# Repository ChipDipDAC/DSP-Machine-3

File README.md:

# DSP-Machine-3<br>
<a class="link" href="https://www.chipdip.ru/catalog-show/for-you-projects?p.0=ChipDipDac"><strong>DSP Machine 3</strong></a> - стример, цифроаналоговый преобразователь ЦАП, аудиопроцессор, для микрокомпьютера Raspberry Pi.<br />
Для построения стримера вы можете использовать любой микрокомпьютер Raspberry Pi. Микрокомпьютер устанавливается на 40-пиновый разъем аудио карты. В качестве ПО используйте любой плеер или ОС образ, которых записан на микроSD карточку для Raspberry Pi. Операционные системы автоматически определяют аудиокарту ChipDip DAC и настраивают вывод звука именно на неё. В некоторых плеерах может понадобится выбрать в качестве устройства вывода звука - ChipDip DAC.<br />
<br />
- Plug and Play не требует пайки<br />
- Совместим с Raspberry Pi 4<br />
- Официальная поддержка RaspberryPi OS / Volumio3 / rAudio1 / Album Player / OpenELEC / Manjaro OS / MoOde и другими.<br />
- Высококачественный аудиопроцессор ADAU1452 и ЦАП AD1934.<br />
- Разъемы аудиовыхода: 2 x XLR (левый и правый), SPDIF, Coaxial<br />
- Встроенная EEPROM для автоматической настройки ОС (с защитой от записи).<br />
- Автоматическое переключение частот в соответствии с входными сигналами I2S.<br />
- Диапазон частот дискретизации и разрядности от 44,1кГц/16 бит до 192кГц/32 бит<br />
- Цветова индикация частот дискретизации<br />
- Совместим с ПО SigmaStudio и ChipStudio для перестройки аудиопроцессора<br />
Задать вопросы можно на форуме в разделе <a class="link" href="https://forum.chipdip.ru/index.php#chipdip-dac.39">ChipDip DAC</a>
<p></p>

<p></p>

<h2>Что под крышкой *</h2>

<p></p>

<p></p>
* Микрокомпьютер Raspberry Pi в комплект не входит.

<h2>Цветовая индикация частоты преобразования (sample rate)</h2>

<table class="user_t">
	<tbody>
		<tr>
			<td class="tcenter">
			<p><strong>Sample Rate</strong></p>
			</td>
			<td class="tcenter">
			<p><strong>Цвет индикатора</strong></p>
			</td>
		</tr>
		<tr>
			<td class="tcenter">44.1 кГц</td>
			<td class="tcenter"></td>
		</tr>
		<tr>
			<td class="tcenter">48 кГц</td>
			<td class="tcenter"></td>
		</tr>
		<tr>
			<td class="tcenter">88.2 кГц</td>
			<td class="tcenter"></td>
		</tr>
		<tr>
			<td class="tcenter">96 кГц</td>
			<td class="tcenter"></td>
		</tr>
		<tr>
			<td class="tcenter">176.4 кГц</td>
			<td class="tcenter"></td>
		</tr>
		<tr>
			<td class="tcenter">192 кГц</td>
			<td class="tcenter"></td>
		</tr>
	</tbody>
</table>

<h2>Сравнительная таблица</h2>

<table class="user_t">
	<tbody>
		<tr>
			<td class="tcenter">&nbsp;</td>
			<td class="tcenter">DSP Machine 1</td>
			<td class="tcenter">DSP Machine 2</td>
			<td class="tcenter">DSP Machine 3</td>
		</tr>
		<tr>
			<td class="tcenter">Темброблок</td>
			<td class="tcenter">+</td>
			<td class="tcenter">+</td>
			<td class="tcenter">+</td>
		</tr>
		<tr>
			<td class="tcenter">SuperBass</td>
			<td class="tcenter">+</td>
			<td class="tcenter">+</td>
			<td class="tcenter">+</td>
		</tr>
		<tr>
			<td class="tcenter">Mute</td>
			<td class="tcenter">+</td>
			<td class="tcenter">+</td>
			<td class="tcenter">+</td>
		</tr>
		<tr>
			<td class="tcenter">Блок питания</td>
			<td class="tcenter">+</td>
			<td class="tcenter">+</td>
			<td class="tcenter">+</td>
		</tr>
		<tr>
			<td class="tcenter">Корректное выключение</td>
			<td class="tcenter">+</td>
			<td class="tcenter">+</td>
			<td class="tcenter">+</td>
		</tr>
		<tr>
			<td class="tcenter">Линейный выход</td>
			<td class="tcenter">-</td>
			<td class="tcenter">+</td>
			<td class="tcenter">+</td>
		</tr>
		<tr>
			<td class="tcenter">Усилитель мощности</td>
			<td class="tcenter">+</td>
			<td class="tcenter">-</td>
			<td class="tcenter">-</td>
		</tr>
		<tr>
			<td class="tcenter">Выход SPDIF</td>
			<td class="tcenter">-</td>
			<td class="tcenter">-</td>
			<td class="tcenter">+</td>
		</tr>
		<tr>
			<td class="tcenter">Выход Toslink</td>
			<td class="tcenter">-</td>
			<td class="tcenter">-</td>
			<td class="tcenter">+</td>
		</tr>
		<tr>
			<td class="tcenter">SigmaStudio</td>
			<td class="tcenter">+</td>
			<td class="tcenter">-</td>
			<td class="tcenter">+</td>
		</tr>
		<tr>
			<td class="tcenter">PurePathStudio</td>
			<td class="tcenter">-</td>
			<td class="tcenter">+</td>
			<td class="tcenter">-</td>
		</tr>
		<tr>
			<td class="tcenter">ChipStudio</td>
			<td class="tcenter">+</td>
			<td class="tcenter">+</td>
			<td class="tcenter">+</td>
		</tr>
	</tbody>
</table>
<br />

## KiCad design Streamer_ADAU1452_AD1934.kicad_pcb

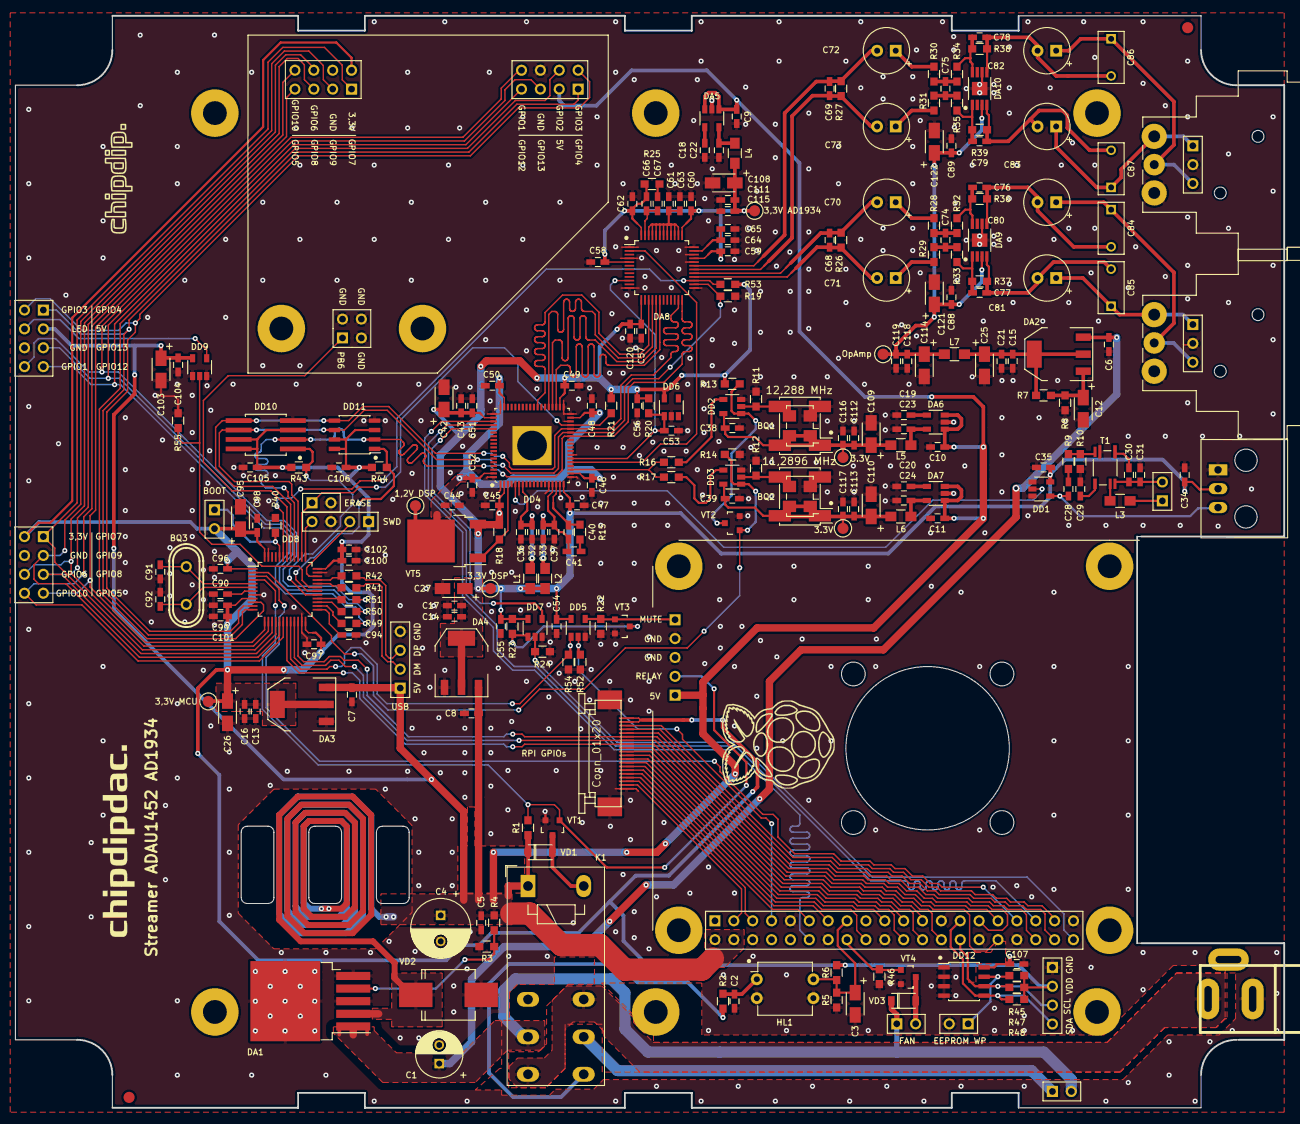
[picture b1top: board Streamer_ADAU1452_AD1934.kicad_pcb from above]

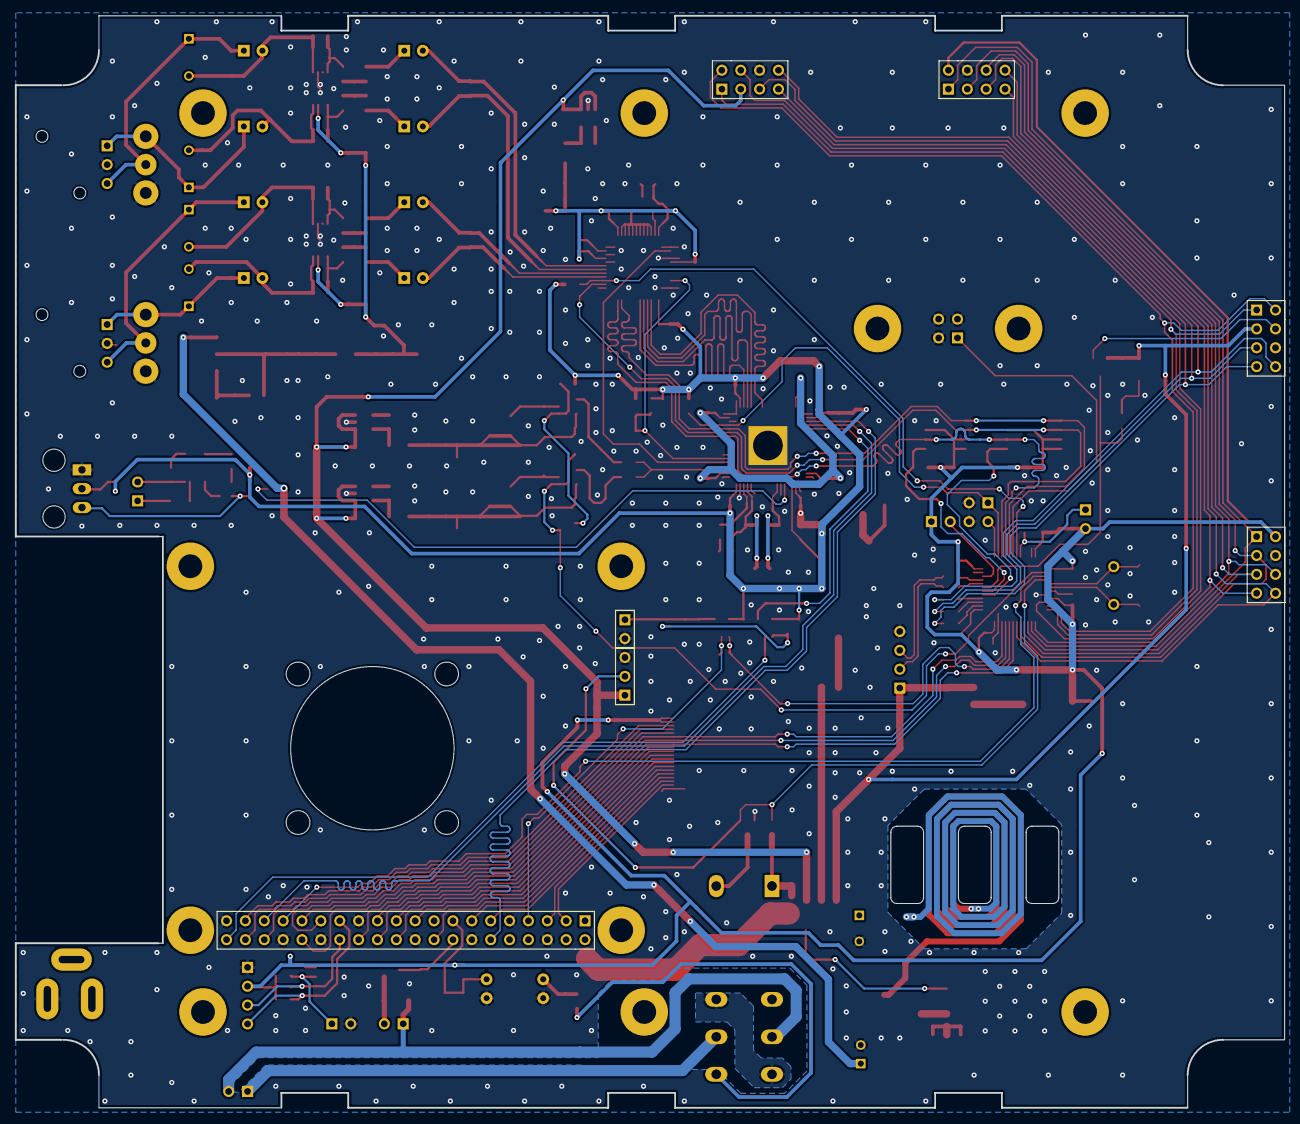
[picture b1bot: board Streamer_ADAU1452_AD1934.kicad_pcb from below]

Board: 2 copper layers, 170.8 x 147.0 mm, 252 parts (7 on the bottom side), 148 nets.

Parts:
BQ1: 12,288MHz; Oscillator_SMD_Fordahl_DFAS2-4Pin_7.3x5.1mm_HandSoldering
BQ2: 11,2896MHz; Oscillator_SMD_Fordahl_DFAS2-4Pin_7.3x5.1mm_HandSoldering
BQ3: 8 Mhz; CRYST_hc-49u_mm
BQ4: 12,288MHz; Oscillator_SMD_EuroQuartz_XO53-4Pin_5.0x3.2mm_HandSoldering
BQ5: 11,2896MHz; Oscillator_SMD_EuroQuartz_XO53-4Pin_5.0x3.2mm_HandSoldering
C1: 100u; C_Radial_D6.3_L11.2_P2.5
C2, C32, C33, C43, C44, C63, C65, C120: 10u; C_0603_HandSoldering
C3, C12, C25, C26, C27, C42, C95, C103, C108, C109, C110, C114, C121, C122: 4.7u; TantalC_SizeA_EIA-3216_mm
C4: 1000u; C_Radial_D8_L11.5_P3.5
C5, C6, C7, C8, C9, C10, C11, C13, C14, C15, C16, C17, C21, C22, C23, C24, C96, C101, C102, C111, C112, C113, C118: 2.2u; C_0603_HandSoldering
C18, C19, C20, C28: 0.01u; C_0603_HandSoldering
C29, C30, C34, C35, C36, C37, C38, C39, C45, C46, C47, C48, C49, C50, C51, C52, C53, C54, C55, C56, C57, C58, C59, C60, C61, C62, C64, C88, C89, C90, C97, C98, C99, C100, C104, C105, C106, C107, C115, C116, C117, C119: 0.1u; C_0603_HandSoldering
C31, C91, C92: 22p; C_0603_HandSoldering
C40, C76, C77, C78, C79: 150p; C_0603_HandSoldering
C41, C67: 5n6; C_0603_HandSoldering
C66: 390p; C_0603_HandSoldering
C68, C69: 1n; C_0603_HandSoldering
C70, C71, C72, C73, C80, C81, C82, C83: 10u; CP_Radial_Tantal_D6.0mm_P2.50mm
C74, C75: 470p; C_0603_HandSoldering
C84, C85, C86, C87: 0.47u; C_Rect_L7_W3.5_P5
C94: 47p; C_0603_HandSoldering
DA1: LM2596S-ADJ; TO-263-5_TabPin3
DA2, DA3, DA4: LM1117-3.3; SOT-223
DA5, DA6, DA7: LP2985-3.3; SOT-23-5_mm
DA8: AD1934; LQFP-48_7x7mm_Pitch0.5mm
DA9, DA10: OPA1632; VSSOP-8
DD1, DD2, DD3, DD7: 74LVC1G125; SOT-23-5_mm
DD4: ADAU1452; LFCSP72_10x10_EP_Handsoldering
DD5: NC7S08M5X; SOT-23-5_mm
DD6: ADM6316; SOT-23-5_mm
DD8: STM32L433CCTx; LQFP-48_7x7mm_Pitch0.5mm
DD9: MC74VHC1GT125; SOT-23-5_mm
DD10: 25LCxxx; SOIC-8_combo_Pitch1.27mm
DD11: 25LCxxx; SOIC-8_3.9x4.9mm_Pitch1.27mm
DD12: 24LC64; SOIC-8_3.9x4.9mm_Pitch1.27mm
HL1: P814; DIP-4_W7.62mm
K1: RTE2xxxx; Relay_DPDT_Schrack-RT2-FormC_RM5mm
L1, L2, L3, L4, L5, L6, L7: L; R_0805_HandSoldering
P3, P4, P5, P6, P7, P8, P9: Conn_01x01; Measurement_Point_Round-SMD-Pad_Small
R1, R6, R7, R8, R11, R12, R13, R14, R19, R20, R21, R22, R23, R24, R36, R37, R38, R39, R40, R43, R44, R45, R46, R49, R50, R51, R52, R53, R54, R55: 10k; R_0603
R2: 2k; R_0603
R3, R18: 1k; R_0603
R4: 3k; R_0603
R5: 15k; R_0603
R9: 470R; R_0603
R10: 110R; R_0603
R15: 4k32; R_0603
R16, R17: 51R; R_0603
R25: 560; R_0603
R26, R27: 100k; R_0603
R28, R29, R30, R31, R32, R33, R34, R35: 2k2; R_0603
R41, R42: 22; R_0603
R47, R48: 4k7; R_0603
T1: ALT4532M; ALT4532
VD1, VD3: D; SOD-123
VD2: D_Schottky; DIODE_SMC_Handsoldering
VT1, VT2, VT3, VT4: BSS138; SOT-23_mm
VT5: STD2805; TO-252-2
XP1, XP14, XP15: Conn_01x03; Pin_Header_Straight_1x03_mm
XP2: Conn_01x03; Optic_FCR6842031T
XP3, XP6, XP8, XP9, XP11, XP13: Conn_01x02; Pin_Header_Straight_1x02_mm
XP4, XP5: XLR3; Jack_XLR_Neutrik_NC3MAAH-1_Horizontal
XP7, XP10, XP12: Conn_01x04; Pin_Header_Straight_1x04_mm
XS1: Conn_01x03; JACK_DC
XS2: Conn_01x02; Pin_Header_Straight_1x02_mm
XS3: Conn_02x20_Odd_Even; Pin_Header_Straight_2x20_mm
XS4, XS5, XS7, XS8: Conn_02x04_Odd_Even; Pin_Header_Straight_2x04_mm
XS6: Conn_01x20; CONN20
XS9: Conn_02x02_Odd_Even; Pin_Header_Straight_2x02_mm

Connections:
5V: C4.1, C5.1, C7.1, C8.1, C9.1, C10.1, C11.1, C103.1, C104.1, DA1.2, DA3.3, DA4.3, DA5.1, DA5.3, DA6.1, DA6.3, DA7.1, DA7.3, DD9.5, K1.A1, R1.1, R4.1, VD1.1, VD2.1, XP1.1, XP10.1, XS3.2, XS3.4, XS5.3, XS8.3
12V: K1.14, K1.22, XS1.1
BCLK: DD4.57, XS3.12
BOOT: DD8.44, R40.1, XP6.1
DATA: DD7.2, R24.2, XS3.40
DSP_BCLK0: DA8.17, DD4.40
DSP_LR0: DA8.18, DD4.39
DSP_RST: C53.1, DA8.10, DD4.24, DD6.1, R20.2
DSP_SDATA0: DA8.16, DD4.41
DSP_SDATA1: DA8.15, DD4.44
DVDD: C44.1, C46.1, C48.1, C50.1, C52.1, DD4.20, DD4.35, DD4.53, DD4.71, P6.1, VT5.2
FAN: R46.1, VT4.1, XS3.16
GEN_SEL: DD3.1, DD8.2, R14.1, VT2.1
GND: BQ1.2, BQ2.2, BQ4.2, BQ5.2, C1.2, C2.2, C3.2, C4.2, C5.2, C6.2, C7.2, C8.2, C9.2, C10.2, C11.2, C12.2, C13.2, C14.2, C15.2, C16.2, C17.2, C18.2, C19.2, C20.2, C21.2, C22.2, C23.2, C24.2, C25.2, C26.2, C27.2, C29.2, C31.2, C32.2, C33.2, C34.2, C35.2, C36.2, C37.2, C38.2, C39.2, C42.2, C43.2, C44.2, C45.2, C46.2, C47.2, C48.2, C49.2, C50.2, C51.2, C52.2, C53.2, C54.2, C55.2, C56.2, C57.2, C58.2, C59.2, C60.2, C61.2, C62.2, C63.2, C64.2, C65.2, C88.1, C89.1, C90.2, C91.2, C92.2, C94.2, C95.2, C96.2, C97.2, C98.2, C99.2, C100.2, C101.2, C102.2, C103.2, C104.2, C105.2, C106.2, C107.2, C108.2, C109.2, C110.2, C111.2, C112.2, C113.2, C114.2, C115.2, C116.2, C117.2, C118.2, C119.2, C120.2, C121.2, C122.2, DA1.3, DA1.5, DA3.1, DA4.1, DA5.2, DA6.2, DA7.2, DA8.1, DA8.4, DA8.12, DA8.25, DA8.32, DA8.34, DA8.36, DA9.6, DA9.9, DA10.6, DA10.9, DD1.1, DD1.3, DD2.3, DD3.3, DD4.1, DD4.6, DD4.14, DD4.17, DD4.19, DD4.25, DD4.34, DD4.36, DD4.37, DD4.54, DD4.55, DD4.72, DD4.73, DD5.3, DD6.2, DD7.3, DD8.8, DD8.23, DD8.35, DD8.47, DD9.1, DD9.3, DD10.4, DD11.4, DD12.1, DD12.2, DD12.3, DD12.4, HL1.2, HL1.3, R3.1, R5.2, R8.2, R10.2, R11.1, R12.1, R14.2, R19.1, R22.2, R24.1, R40.2, R46.2, R52.1, R54.1, R55.2, T1.2, VD2.2, VT1.2, VT2.2, VT3.2, VT4.2, XP1.3, XP2.1, XP3.2, XP4.1, XP5.1, XP7.3, XP8.2, XP10.4, XP11.2, XP12.1, XP14.2, XP15.2, XS1.2, XS3.6, XS3.9, XS3.14, XS3.20, XS3.25, XS3.30, XS3.34, XS3.39, XS4.4, XS5.6, XS6.20, XS7.4, XS8.6, XS9.2, XS9.3, XS9.4
GPIO0: DA8.27, DD8.43, R53.2
GPIO1: R51.1, XS5.8, XS8.8
GPIO2: DD8.10, XS8.4
GPIO3: DD8.11, XS5.2, XS8.2
GPIO4: DD8.12, XS5.1, XS8.1
GPIO5: DD8.13, XS4.7, XS7.7
GPIO6: DD8.14, XS4.6, XS7.6
GPIO7: DD8.15, XS4.1, XS7.1
GPIO8: DD8.16, XS4.5, XS7.5
GPIO9: DD8.17, XS4.3, XS7.3
GPIO10: DD8.18, XS4.8, XS7.8
GPIO12: R49.1, XS5.7, XS8.7
GPIO13: R50.1, XS5.5, XS8.5
ID_SCL: DD12.6, R47.2, XP12.3, XS3.28
ID_SDA: DD12.5, R48.2, XP12.4, XS3.27
LED_OUT: DD9.4, XS5.4
LR: DD4.58, XS3.35
MCLK_OUT: DA8.2, DD4.23
MUTE: DD5.2, R52.2, XS3.7
MUTE2: DD5.1, DD8.20, R54.2
MUTE_OUT: DA9.7, DA10.7, DD5.4, R22.1, VT3.1, XP3.1
unnamed: BQ1.3, BQ4.3, DD2.2, R11.2
unnamed: BQ2.3, BQ5.3, DD3.2, R12.2
unnamed: BQ3.1, C91.1, DD8.5
unnamed: BQ3.2, C92.1, DD8.6
unnamed: C2.1, HL1.1, R2.2
unnamed: C12.1, DA2.1, R7.2, R8.1
unnamed: C15.1, C21.1, C25.1, DA2.2, DA2.4, L7.1, R7.1
unnamed: C18.1, DA5.4
unnamed: C19.1, DA6.4
unnamed: C20.1, DA7.4
unnamed: C22.1, DA5.5, L4.1
unnamed: C23.1, DA6.5, L5.1
unnamed: C24.1, DA7.5, L6.1
unnamed: C28.1, R9.2
unnamed: C29.1, T1.6
unnamed: C30.1, T1.3
unnamed: C30.2, C31.1, T1.4, XS2.2
unnamed: C32.1, C36.1, DD4.7, L1.2
unnamed: C33.1, C37.1, C40.1, C41.1, DD4.15, L2.2
unnamed: C40.2, DD4.16, R15.2
unnamed: C41.2, R15.1
unnamed: C61.1, C63.1, DA8.38, DA8.39, DA8.40, DA8.41, DA8.42, DA8.43, DA8.44, DA8.45, DA8.46
unnamed: C64.1, C65.1, DA8.35
unnamed: C66.1, C67.1, DA8.47
unnamed: C67.2, R25.1
unnamed: C68.1, C70.2, DA8.29, R26.1
unnamed: C68.2, C71.2, DA8.28, R26.2
unnamed: C69.1, C72.2, DA8.31, R27.1
unnamed: C69.2, C73.2, DA8.30, R27.2
unnamed: C70.1, R28.1
unnamed: C71.1, R29.1
unnamed: C72.1, R30.1
unnamed: C73.1, R31.1
unnamed: C74.1, R28.2, R32.1
unnamed: C74.2, R29.2, R33.1
unnamed: C75.1, R30.2, R34.1
unnamed: C75.2, R31.2, R35.1
unnamed: C76.1, C80.2, C84.2, DA9.5, R36.2
unnamed: C76.2, DA9.8, R32.2, R36.1
unnamed: C77.1, C81.2, C85.2, DA9.4, R37.2
unnamed: C77.2, DA9.1, R33.2, R37.1
unnamed: C78.1, C82.2, C86.2, DA10.5, R38.2
unnamed: C78.2, DA10.8, R34.2, R38.1
unnamed: C79.1, C83.2, C87.2, DA10.4, R39.2
unnamed: C79.2, DA10.1, R35.2, R39.1
unnamed: C80.1, C84.1, XP4.3, XP14.3
unnamed: C81.1, C85.1, XP4.2, XP14.1
unnamed: C82.1, C86.1, XP5.3, XP15.3
unnamed: C83.1, C87.1, XP5.2, XP15.1
unnamed: C94.1, DD8.25
unnamed: DA1.4, R3.2, R4.2
unnamed: DD1.2, DD4.5
unnamed: DD2.1, R13.2, VT2.3
unnamed: DD2.4, R16.2
unnamed: DD3.4, R17.2
unnamed: DD4.3, R18.2, VT5.1
unnamed: DD4.21, R16.1, R17.1
unnamed: DD7.1, R23.2, VT3.3
unnamed: DD8.26, R49.2
unnamed: DD8.27, R50.2
unnamed: DD8.28, R51.2
unnamed: DD8.31, DD9.2, R55.1
unnamed: DD8.32, R41.1
unnamed: DD8.33, R42.1
unnamed: DD12.7, R45.2, XP8.1
unnamed: K1.21, XP13.1
unnamed: K1.24, R2.1
unnamed: K1.A2, VD1.2, VT1.3
unnamed: L3.1, T1.5
unnamed: L3.2, XS2.1
unnamed: R9.1, R10.1, T1.1
unnamed: VD3.2, VT4.3, XP9.2
ON_OFF: C3.1, HL1.4, R5.1, R6.2, XS3.15
PB6: DD8.42, XS9.1
PWR_EVENT: DD8.3, XS3.33
RAS_GPIO2: XS3.3, XS6.19
RAS_GPIO3: XS3.5, XS6.18
RAS_GPIO7: XS3.26, XS6.9
RAS_GPIO8: XS3.24, XS6.11
RAS_GPIO9: XS3.21, XS6.12
RAS_GPIO10: XS3.19, XS6.14
RAS_GPIO11: XS3.23, XS6.10
RAS_GPIO16: XS3.36, XS6.5
RAS_GPIO17: XS3.11, XS6.17
RAS_GPIO20: XS3.38, XS6.4
RAS_GPIO25: XS3.22, XS6.13
RAS_GPIO26: XS3.37, XS6.3
RELAY: DD8.4, R1.2, VT1.1, XP1.2
RES0: XS3.18, XS6.15
RES1: XS3.13, XS6.16
RST: C90.1, DD8.7
SDATA_IN0: DD4.59, DD7.4
SPDIF_OUT: C28.2, DD1.4, XP2.3
SPI1_MISO: DA8.24, DD4.30, DD8.40, DD10.2, DD11.2
SPI1_MOSI: DA8.23, DD4.32, DD8.41, DD10.5, DD11.5
SPI1_NSS1: DD4.33, DD8.38, R21.2, XP11.1
SPI1_NSS2: DD8.29, DD10.1, R43.2
SPI1_NSS3: DD8.30, DD11.1, R44.2
SPI1_SCK: DA8.26, DD4.31, DD8.39, DD10.6, DD11.6, R19.2
SR0: DD8.22, XS3.29, XS6.6
SR1: DD8.21, XS3.31, XS6.7
SR2: DD8.19, XS3.32, XS6.8
SWCLK: DD8.37, XP7.4
SWDIO: DD8.34, XP7.2
USB_DM: R41.2, XP10.2
USB_DP: R42.2, XP10.3
VDD: C13.1, C16.1, C26.1, C95.1, C96.1, C97.1, C98.1, C99.1, C100.1, C101.1, C102.1, C105.1, C106.1, C107.1, DA3.2, DA3.4, DD8.1, DD8.9, DD8.24, DD8.36, DD8.48, DD10.3, DD10.7, DD10.8, DD11.3, DD11.7, DD11.8, DD12.8, P4.1, R6.1, R43.1, R44.1, R45.1, R47.1, R48.1, XP6.2, XP7.1, XP12.2, XS4.2, XS6.1, XS6.2, XS7.2
VDDA: C58.1, C59.1, C60.1, C62.1, C66.2, C108.1, C111.1, C115.1, DA8.5, DA8.33, DA8.37, DA8.48, L4.2, P7.1, R25.2
VDD_AOUT: C88.2, C89.2, C114.1, C118.1, C119.1, C121.1, C122.1, DA9.3, DA10.3, L7.2, P3.1
VDD_DSP: C14.1, C17.1, C27.1, C34.1, C35.1, C42.1, C43.1, C45.1, C47.1, C49.1, C51.1, C54.1, C55.1, C56.1, C57.1, C120.1, DA4.2, DA4.4, DA8.13, DD1.5, DD4.2, DD4.18, DD4.38, DD4.56, DD5.5, DD6.5, DD7.5, L1.1, L2.1, P5.1, R13.1, R18.1, R20.1, R21.1, R23.1, R53.1, VT5.3, XP2.2
VDD_GEN1: BQ2.1, BQ2.4, BQ5.1, BQ5.4, C39.1, C110.1, C113.1, C117.1, DD3.5, L6.2, P9.1
VDD_GEN2: BQ1.1, BQ1.4, BQ4.1, BQ4.4, C38.1, C109.1, C112.1, C116.1, DD2.5, L5.2, P8.1
VIN: C1.1, C6.1, DA1.1, DA2.3, K1.11, VD3.1, XP9.1, XP13.2

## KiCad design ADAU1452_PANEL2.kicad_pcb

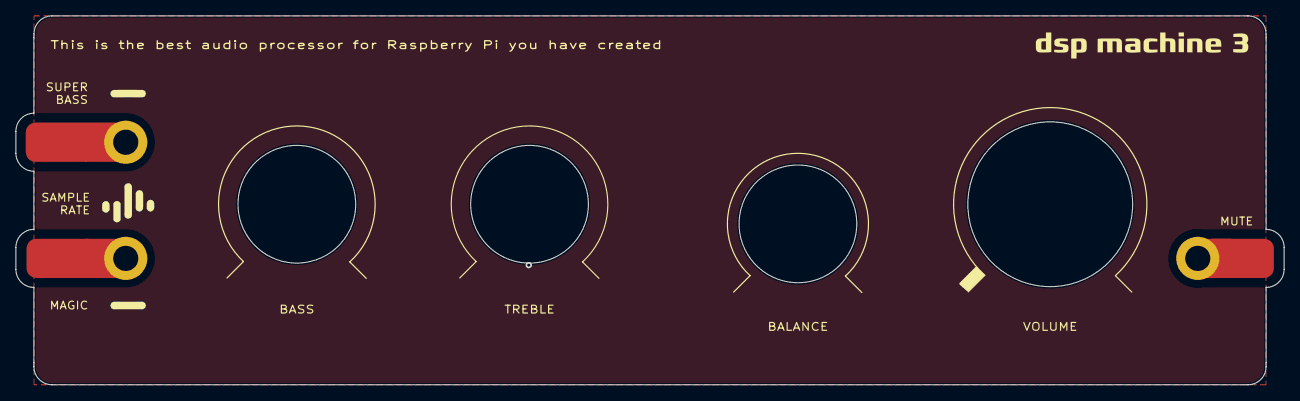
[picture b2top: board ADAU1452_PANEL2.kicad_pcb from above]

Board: 2 copper layers, 161.6 x 47.0 mm, 7 parts (1 on the bottom side), 3 nets.

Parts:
J1, J2, J3: Conn_01x01_Male; TestPoint_THTPad_D2.0mm_Drill1.0mm
TP1, TP1#2, TP3, TP6: TestPoint; TestPoint_Pad_4.0x4.0mm

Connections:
unnamed: J1.1, TP1.1
unnamed: J2.1, TP1#2.1
unnamed: J3.1, TP6.1
